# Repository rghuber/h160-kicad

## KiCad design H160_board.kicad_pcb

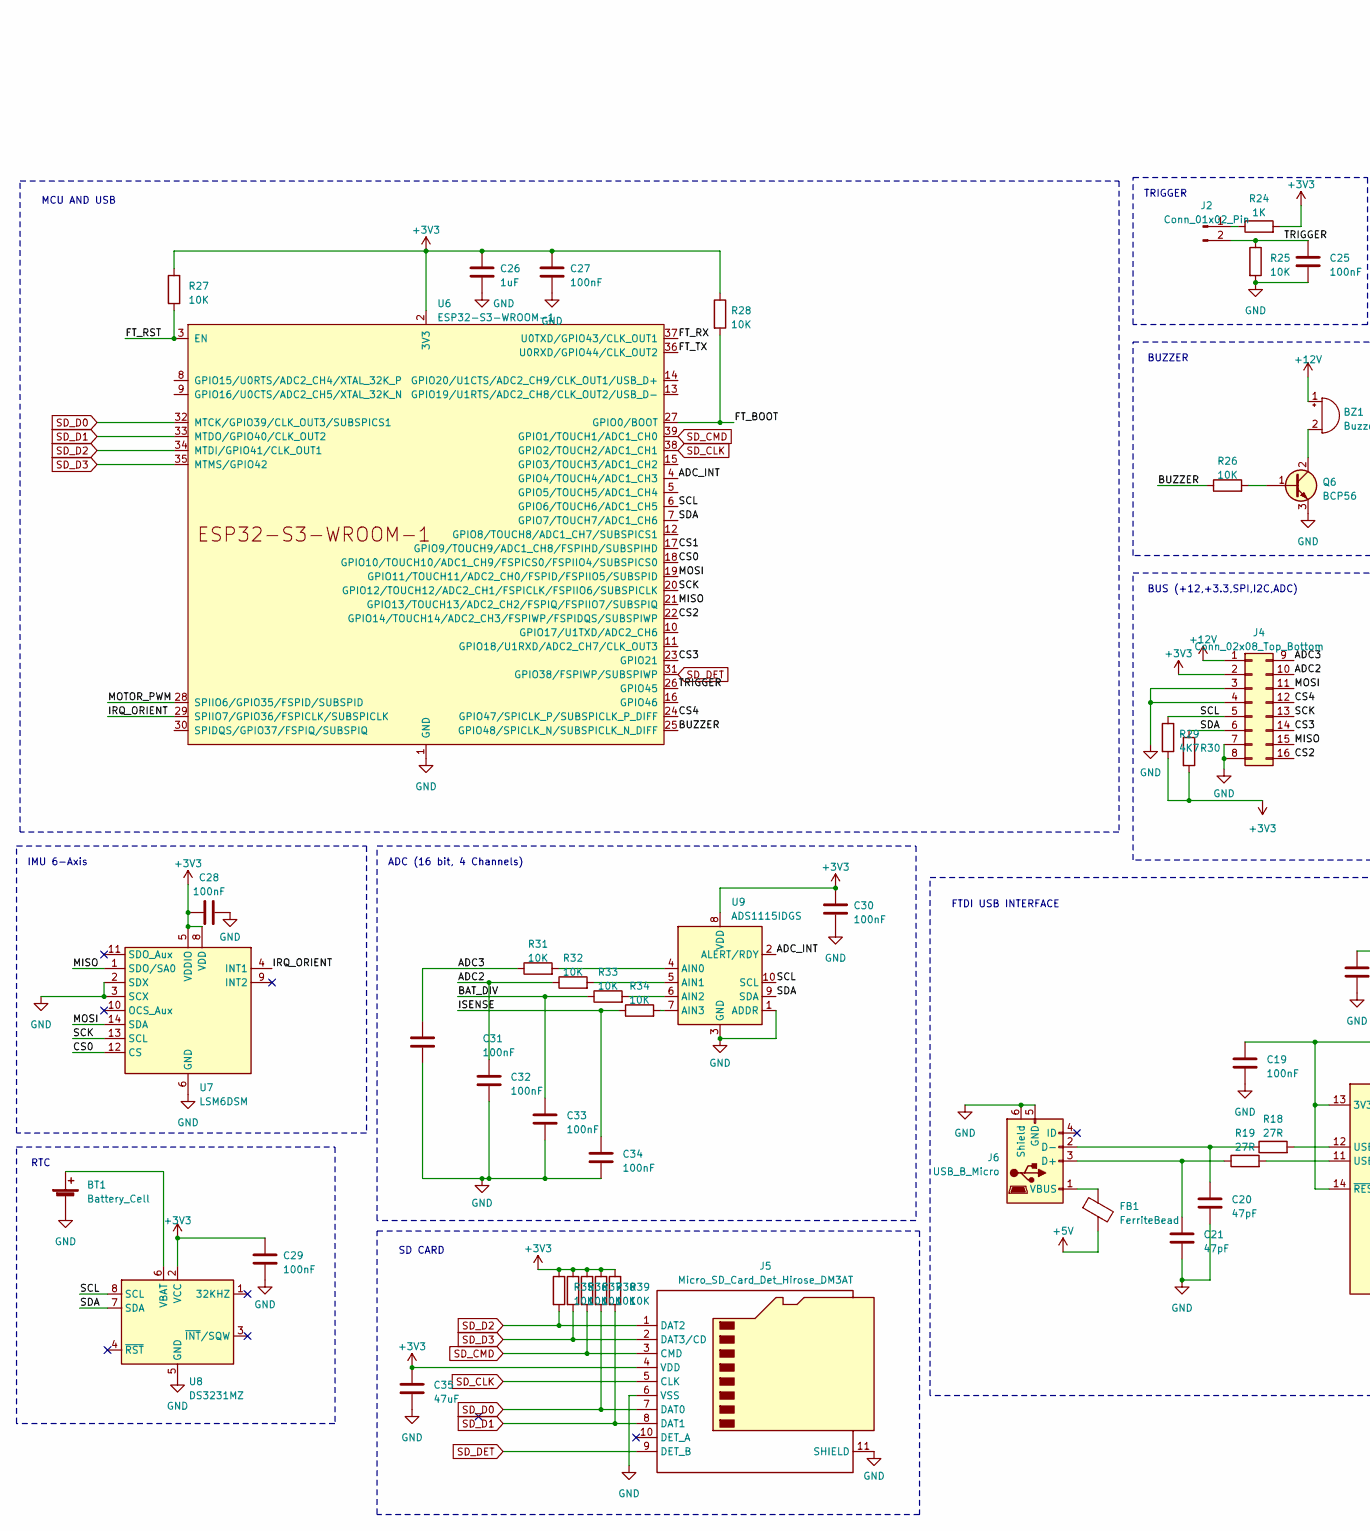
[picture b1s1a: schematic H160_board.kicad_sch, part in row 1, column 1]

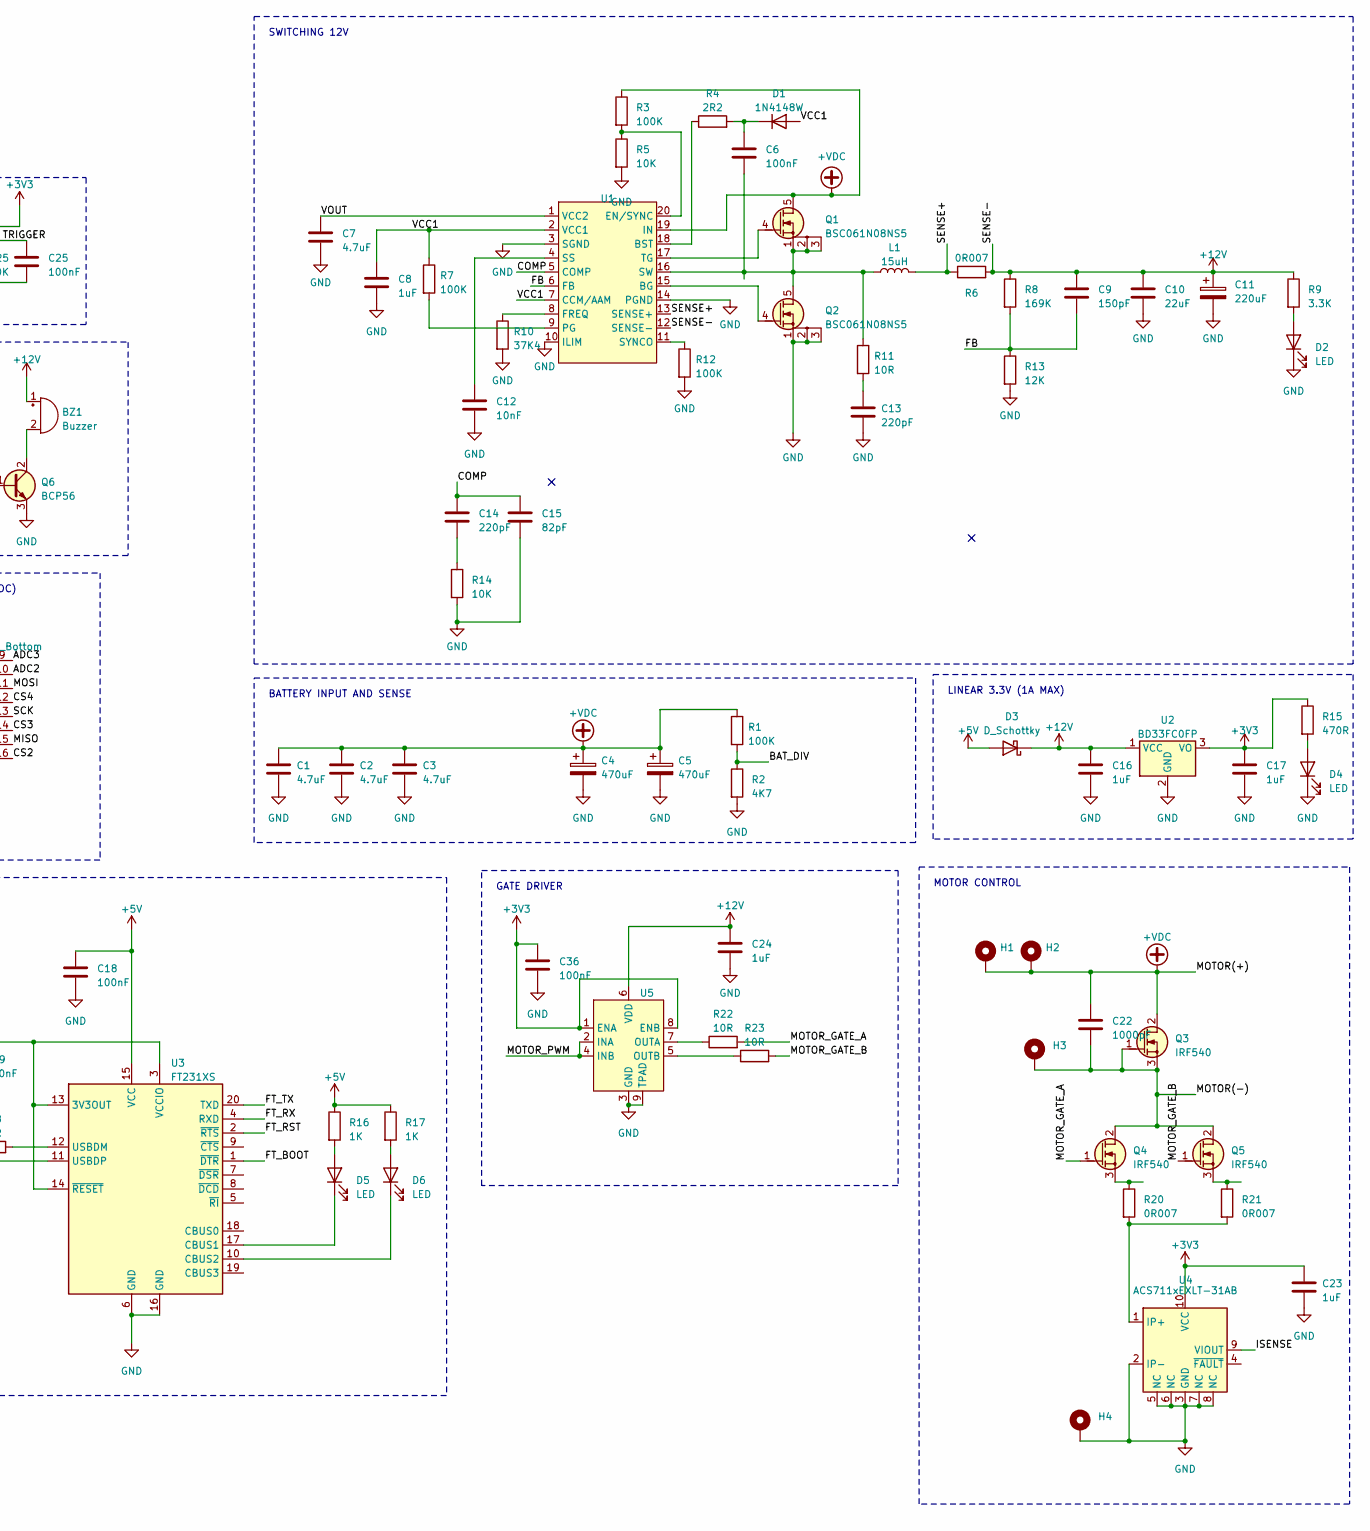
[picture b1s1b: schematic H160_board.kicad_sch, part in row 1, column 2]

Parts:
BT1: Battery_Cell; BatteryHolder_Keystone_1060_1x2032
BZ1: Buzzer; Buzzer_12x9.5RM7.6
C1, C2, C3: 4.7uF; R_1206_3216Metric_Pad1.30x1.75mm_HandSolder
C4, C5: 470uF; CP_Radial_D12.5mm_P5.00mm
C6, C18, C19, C25, C27, C28, C29, C30, C31, C32, C33, C34, C36: 100nF; C_0603_1608Metric
C7: 4.7uF; C_0603_1608Metric
C8, C23: 1uF; C_0603_1608Metric
C9: 150pF; C_0603_1608Metric
C10: 22uF; C_1812_4532Metric
C11: 220uF; CP_Elec_6.3x4.5
C12: 10nF; C_0603_1608Metric
C13, C14: 220pF; C_0603_1608Metric
C15: 82pF; C_0603_1608Metric
C16, C17, C26: 1uF; C_1206_3216Metric
C20, C21: 47pF; C_0603_1608Metric
C22: 1000pF; C_1812_4532Metric
C24: 1uF; C_1812_4532Metric
C35: 47uF; C_0805_2012Metric
D1: 1N4148W; D_SOD-123
D2, D4, D5, D6: LED; LED_0805_2012Metric
D3: D_Schottky; D_SOD-123F
FB1: FerriteBead; C_0603_1608Metric
H1, H4: MountingHole_Pad; MountingHole_3.7mm_Pad_TopBottom
H2, H3: MountingHole_Pad; MountingHole_5mm_PTH_TopBottom
J2: Conn_01x02_Pin; PinHeader_1x02_P2.54mm_Vertical
J4: Conn_02x08_Top_Bottom; PinHeader_2x08_P2.54mm_Vertical
J5: Micro_SD_Card_Det_Hirose_DM3AT; microSD_HC_Hirose_DM3AT-SF-PEJM5
J6: USB_B_Micro; USB_Micro-B_Amphenol_10103594-0001LF_Horizontal
L1: 15uH; L_12x12mm_H8mm
Q1, Q2: BSC061N08NS5; Infineon_PG-TDSON-8
Q3, Q4, Q5: IRF540; TO-220-3_Vertical_GDS
Q6: BCP56; SOT-223-3_TabPin2
R1, R3, R7, R12: 100K; R_0603_1608Metric
R2, R29, R30: 4K7; R_0603_1608Metric
R4: 2R2; R_0603_1608Metric
R5, R14, R25, R26, R27, R28, R31, R32, R33, R34, R35, R36, R37, R38, R39: 10K; R_0603_1608Metric
R6, R20, R21: 0R007; R_2512_6332Metric
R8: 169K; R_0603_1608Metric
R9: 3.3K; R_0603_1608Metric
R10: 37K4; R_0603_1608Metric
R11, R22, R23: 10R; R_0603_1608Metric
R13: 12K; R_0603_1608Metric
R15: 470R; R_0603_1608Metric
R16, R17, R24: 1K; R_0603_1608Metric
R18, R19: 27R; R_0603_1608Metric
U1: QFN-20-1EP_3x4mm_P0.5mm_EP1.65x2.65mm
U2: BD33FC0FP; TO-252-2
U3: FT231XS; SSOP-20_3.9x8.7mm_P0.635mm
U4: ACS711xEXLT-31AB; Allegro_QFN-12-10-1EP_3x3mm_P0.5mm
U5: Infineon_PG-DSO-8-27_3.9x4.9mm_EP2.65x3mm_ThermalVias
U6: ESP32-S3-WROOM-1
U7: LSM6DSM; LGA-14_3x2.5mm_P0.5mm_LayoutBorder3x4y
U8: DS3231MZ; SOIC-8_3.9x4.9mm_P1.27mm
U9: ADS1115IDGS; 10-XFQFN

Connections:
+3V3: C17.1, C23.1, C26.1, C27.1, C28.1, C29.1, C30.1, C35.1, C36.1, J4.2, J5.4 (VDD), R15.1, R24.2, R27.2, R28.1, R29.2, R30.2, R35.1, R36.1, R37.1, R38.1, R39.1, U2.3 (VO), U4.10 (VCC), U5.1 (ENA), U5.8 (ENB), U6.2 (3V3), U7.5 (VDDIO), U7.8 (VDD), U8.2 (VCC), U9.8 (VDD)
+5V: C18.1, D3.2 (A), FB1.2, R16.1, R17.1, U3.15 (VCC)
+12V: BZ1.1 (-), C9.1, C10.1, C11.1, C16.1, C24.1, D3.1 (K), J4.1, R6.2, R8.1, R9.1, U1.12 (SENSE-), U2.1 (VCC), U5.6 (VDD)
+VDC: C1.1, C2.1, C3.1, C4.1, C5.1, C22.1, H1.1, H2.1, Q1.5 (D), Q3.2 (D), R1.1, R3.1, U1.19 (IN)
/ADC2: C32.1, J4.10, R32.1
/ADC3: C31.1, J4.9, R31.1
/ADC_INT: U6.4 (GPIO4/TOUCH4/ADC1_CH3), U9.2 (ALERT/RDY)
/BAT_DIV: C33.1, R1.2, R2.1, R33.1
/BUZZER: R26.1, U6.25 (GPIO48/SPICLK_N/SUBSPICLK_N_DIFF)
/COMP: C14.1, C15.1, U1.5 (COMP)
/CS0: U6.18 (GPIO10/TOUCH10/ADC1_CH9/FSPICS0/FSPIIO4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), U7.12 (CS)
/CS1: U6.17 (GPIO9/TOUCH9/ADC1_CH8/FSPIHD/SUBSPIHD)
/CS2: J4.16, U6.22 (GPIO14/TOUCH14/ADC2_CH3/FSPIWP/FSPIDQS/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)
/CS3: J4.14, U6.23 (GPIO21)
/CS4: J4.12, U6.24 (GPIO47/SPICLK_P/SUBSPICLK_P_DIFF)
/FB: C9.2, R8.2, R13.1, U1.6 (FB)
/FT_BOOT: R28.2, U3.1 (~DTR), U6.27 (GPIO0/BOOT)
/FT_RST: R27.1, U3.2 (~RTS), U6.3 (EN)
/FT_RX: U3.4 (RXD), U6.37 (U0TXD/GPIO43/CLK_OUT1)
/FT_TX: U3.20 (TXD), U6.36 (U0RXD/GPIO44/CLK_OUT2)
/IRQ_ORIENT: U6.29 (SPIIO7/GPIO36/FSPICLK/SUBSPICLK), U7.4 (INT1)
/ISENSE: C34.1, R34.1, U4.9 (VIOUT)
/MISO: J4.15, U6.21 (GPIO13/TOUCH13/ADC2_CH2/FSPIQ/FSPIIO7/S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), U7.1 (SDO/SA0)
/MOSI: J4.11, U6.19 (GPIO11/TOUCH11/ADC2_CH0/FSPID/FSPIIO5/S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), U7.14 (SDA)
/MOTOR(-): C22.2, H3.1, Q3.1 (G), Q3.3 (S), Q4.2 (D), Q5.2 (D)
/MOTOR_GATE_A: Q4.1 (G), R22.2
/MOTOR_GATE_B: Q5.1 (G), R23.2
/MOTOR_PWM: U5.2 (INA), U5.4 (INB), U6.28 (SPIIO6/GPIO35/FSPID/SUBSPID)
/SCK: J4.13, U6.20 (GPIO12/TOUCH12/ADC2_CH1/FSPICLK/FSPIIO6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), U7.13 (SCL)
/SCL: J4.5, R29.1, U6.6 (GPIO6/TOUCH6/ADC1_CH5), U8.8 (SCL), U9.10 (SCL)
/SDA: J4.6, R30.1, U6.7 (GPIO7/TOUCH7/ADC1_CH6), U8.7 (SDA), U9.9 (SDA)
/SENSE+: L1.2, R6.1, U1.13 (SENSE+)
/TRIGGER: C25.1, J2.2, R25.1, U6.26 (GPIO45)
/VCC1: C8.1, D1.2 (A), R7.1, U1.2 (VCC1), U1.7 (CCM/AAM)
/VOUT: C7.1, U1.1 (VCC2)
GND: BT1.2 (-), C1.2, C2.2, C3.2, C4.2, C5.2, C7.2, C8.2, C10.2, C11.2, C12.2, C13.2, C15.2, C16.2, C17.2, C18.2, C19.2, C20.2, C21.2, C23.2, C24.2, C25.2, C26.2, C27.2, C28.2, C29.2, C30.2, C31.2, C32.2, C33.2, C34.2, C35.2, C36.2, D2.1 (K), D4.1 (K), H4.1, J4.3, J4.4, J4.7, J4.8, J5.6 (VSS), J5.11 (SHIELD), J6.5 (GND), J6.6 (Shield), Q2.1 (S), Q2.2 (S), Q2.3 (S), Q6.3 (E), R2.2, R5.2, R10.2, R12.2, R13.2, R14.2, R25.2, U1.3 (SGND), U1.10 (ILIM), U1.14 (PGND), U2.2 (GND), U3.6 (GND), U3.16 (GND), U4.2 (IP-), U4.3 (GND), U4.5 (NC), U4.6 (NC), U4.7 (NC), U4.8 (NC), U5.3 (GND), U5.9 (TPAD), U6.1 (GND), U6.40 (GND), U6.41 (GND), U7.2 (SDX), U7.3 (SCX), U7.6 (GND), U7.7 (GND), U8.5 (GND), U9.1 (ADDR), U9.3 (GND)
unnamed: BT1.1 (+), U8.6 (VBAT)
unnamed: BZ1.2 (+), Q6.2 (C)
unnamed: C13.1, R11.2
unnamed: C14.2, R14.1
unnamed: C6.1, D1.1 (K), R4.2
unnamed: D2.2 (A), R9.2
unnamed: D4.2 (A), R15.2
unnamed: D5.2 (A), R16.2
unnamed: D5.1 (K), U3.17 (CBUS1)
unnamed: D6.2 (A), R17.2
unnamed: D6.1 (K), U3.10 (CBUS2)
unnamed: J2.1, R24.1
unnamed: C21.1, J6.3 (D+), R19.1
unnamed: C20.1, J6.2 (D-), R18.1
unnamed: FB1.1, J6.1 (VBUS)
unnamed: Q1.4 (G), U1.17 (TG)
unnamed: C6.2, L1.1, Q1.1 (S), Q1.2 (S), Q1.3 (S), Q2.5 (D), R11.1, U1.16 (SW)
unnamed: Q2.4 (G), U1.15 (BG)
unnamed: Q4.3 (S), R20.1
unnamed: Q5.3 (S), R21.1
unnamed: Q6.1 (B), R26.2
unnamed: R4.1, U1.18 (BST)
unnamed: R3.2, R5.1, U1.20 (EN/SYNC)
unnamed: R10.1, U1.8 (FREQ)
unnamed: R7.2, U1.9 (PG)
unnamed: C12.1, U1.4 (SS)
unnamed: R12.1, U1.11 (SYNCO)
unnamed: C19.1, U3.3 (VCCIO), U3.13 (3V3OUT), U3.14 (~RESET)
unnamed: R18.2, U3.12 (USBDM)
unnamed: R19.2, U3.11 (USBDP)
unnamed: R20.2, R21.2, U4.1 (IP+)
unnamed: R22.1, U5.7 (OUTA)
unnamed: R23.1, U5.5 (OUTB)
unnamed: R31.2, U9.4 (AIN0)
unnamed: R32.2, U9.5 (AIN1)
unnamed: R33.2, U9.6 (AIN2)
unnamed: R34.2, U9.7 (AIN3)
SD_CLK: J5.5 (CLK), U6.38 (GPIO2/TOUCH2/ADC1_CH1)
SD_CMD: J5.3 (CMD), R37.2, U6.39 (GPIO1/TOUCH1/ADC1_CH0)
SD_D0: J5.7 (DAT0), R38.2, U6.32 (MTCK/GPIO39/CLK_OUT3/SUBSPICS1)
SD_D1: J5.8 (DAT1), R39.2, U6.33 (MTDO/GPIO40/CLK_OUT2)
SD_D2: J5.1 (DAT2), R35.2, U6.34 (MTDI/GPIO41/CLK_OUT1)
SD_D3: J5.2 (DAT3/CD), R36.2, U6.35 (MTMS/GPIO42)
SD_DET: J5.9 (DET_B), U6.31 (GPIO38/FSPIWP/SUBSPIWP)

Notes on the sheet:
LINEAR 3.3V (1A MAX)
FTDI USB INTERFACE
MCU AND USB
TRIGGER
BATTERY INPUT AND SENSE
BUZZER
ADC (16 bit, 4 Channels)
GATE DRIVER
SD CARD
IMU 6-Axis
SWITCHING 12V
RTC
MOTOR CONTROL
BUS (+12,+3.3,SPI,I2C,ADC)

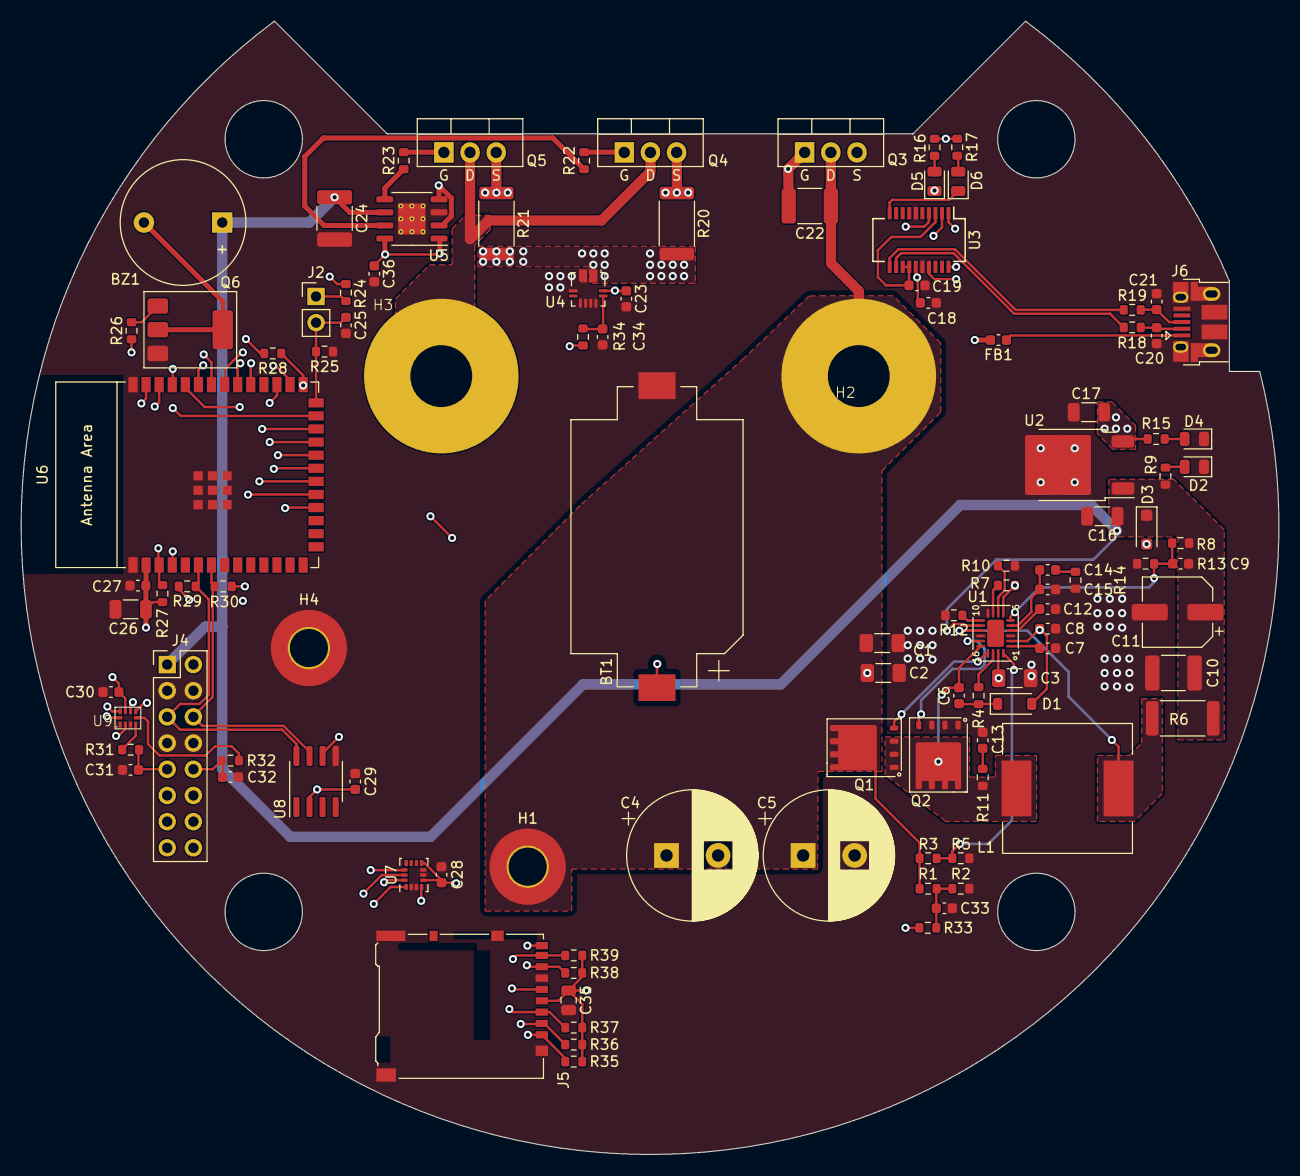
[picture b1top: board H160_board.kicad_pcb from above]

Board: 4 copper layers, 122.0 x 109.9 mm, 108 parts (0 on the bottom side), 79 nets.
